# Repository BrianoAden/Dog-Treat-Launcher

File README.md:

<h1>Dog Treat Dispenser</h1>
<p> This project was for my EDES 301 class. Following is a link to the Hackster.io page I put up detailing the physical build of my project.</p>
<a href="https://www.hackster.io/aden-briano/edes301-dog-treat-launcher-bcfb15">Dog Treat Launcher</a>
<p> Now, I will walk you through the software build required to run this project!</p> 

<h2> Setup </h2>
<p> You are going to need to install the operating system on your PocketBeagle. You will need an SD card and SD card flashing software, like Etcher. 
Download bone-debian-10.11-iot-armhf-2022-02-03-4gb.img.xz from <a href="https://rcn-ee.com/rootfs/bb.org/testing/2022-02-03/buster-iot/">OS</a>. 
Use Etcher to flash your SD card. You can now insert your SD card into your PocketBeagle and plug your PocketBeagle into your laptop. 
Great! Now we can get started. You will need to use the Cloud9 IDE to code on the PocketBeagle using Python. Navigate to http://192.168.6.2:3000/ 
in your browser if you're on mac, or http://192.168.7.2:3000/ if you're on windows. You will also need your Beagle to be connected to the internet for this project. 
There are online resources on how to do this, so I won't walk through it. Once you're on Cloud9, run the following commands.</p>
<p>
                                            $ sudo apt-get update <br>
                                            $ sudo apt-get install build-essential python-dev python-setuptools python-smbus -y <br>
                                            $ sudo apt-get install python-pip python3-pip -y <br>
                                            $ sudo apt-get install zip -y <br>
                                            $ sudo pip3 install --upgrade setuptools <br>
                                            $ sudo pip3 install --upgrade Adafruit_BBIO <br>
                                            $ sudo pip3 install adafruit-blinka <br>
</p>
<p>
Now copy this github repo onto your PocketBeagle using the following command <br>
                                            $ git clone https://github.com/BrianoAden/EDES301 <br>
<h2> Package Installation </h2>
In order to run our project, we need to install the following packages: SpeechRecognition, PyAudio. <br> Let's begin the installation process. Run the following commands. <br>
<br>
$ sudo apt-get update <br>
$ sudo apt-get install -y swig libpulse-dev libasound2-dev <br>
$ sudo apt-get install libportaudio0 libportaudio2 libportaudiocpp0 portaudio19-dev <br>
$ sudo apt-get python-dev <br>
$ sudo python pyaudio/setup.py install <br>
$ sudo python3 -m pip install SpeechRecognition==3.9.0 <br>
<br>

Plug in your USB microphone. Let's check if it's recognized by the PocketBeagle. Run the following command. <br>
$ arecord -l <br>
You should see the following in your output. <br>
<br>
card 1: Device [USB PnP Sound Device], device 0: USB Audio [USB Audio] <br>
  Subdevices: 1/1 <br>
  Subdevice #0: subdevice #0 <br>
<br>
Good, our microphone is almost ready! We just need to set it as our default device. Run the following command. <br>
<br>
$ nano ~/.asoundrc <br>
<br>
Now write in the following. <br>

 <br>

Redundancy is resiliency, so run this just to be safe. <br>
$ sudo apt-get install -y python-pyaudio python3-pyaudio <br>

Now we should be good to go!
</p>
<h2> Software Operation </h2>
Note! You are required to be connected to the internet to run this project, as the recognize_google() method used by SpeechRecognition requires the internet.
If you manage to connect to the internet through your laptop, but when you reboot your PocketBeagle it disconnects, try running the following commands. <br>
<br>
$ sudo dhclient usb1 <br>
<br>
It's going to ask for a password. The password is temppwd. <br>
If you want to run the program, type sudo ./run into your terminal while in the treat_launcher directory. If this doesn't work, run chmod 755 ./run
to make it executable. To auto-run on boot, perform the following. <br>
<br>
$ sudo crontab -e <br>
<br>
Write the following at the bottom of the file <br>
<br>
@reboot sleep 30 && bash /var/lib/cloud9/EDES301/project_01/python/treat_launcher/run > /var/lib/cloud9/logs/cronlog 2>&1<br>
<br>
Now reboot and it should be good! Run the following to kill the processes. <br>
<br>
$ ps -ef <br>
$ sudo kill -9 (process id(s)) <br>
<br>
Now, you should be set to run the project. In each file under EDES301/project_01/python, there are tests you can use to debug a component.
I hope everything goes well, and I hope your dog loves it! Good luck building!

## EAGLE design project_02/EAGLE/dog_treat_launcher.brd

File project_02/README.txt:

Dog Treat Launcher PCB

You want to manufacture this PCB??? Wow you must really love your dog! Or you're just curious and wanted to read this file. Well, in the folder that you found this README inside, "project_02", there are three folders. Inside docs are just some screenshots of different parts of the board. Inside EAGLE, you will find the library I used to create the board, as well as the board's schematic and brd file. Inside MFG are the gerber files that you can use if you feel like spending a pretty penny on manufacturing this board. 
This board is designed after the Dog Treat Launcher I designed and developed in project_01. If you care to learn more about that project, please read the README file in project_01. Following is the link to the hackster page I put up for the project. https://www.hackster.io/aden-briano/edes301-dog-treat-launcher-bcfb15 Enjoy!

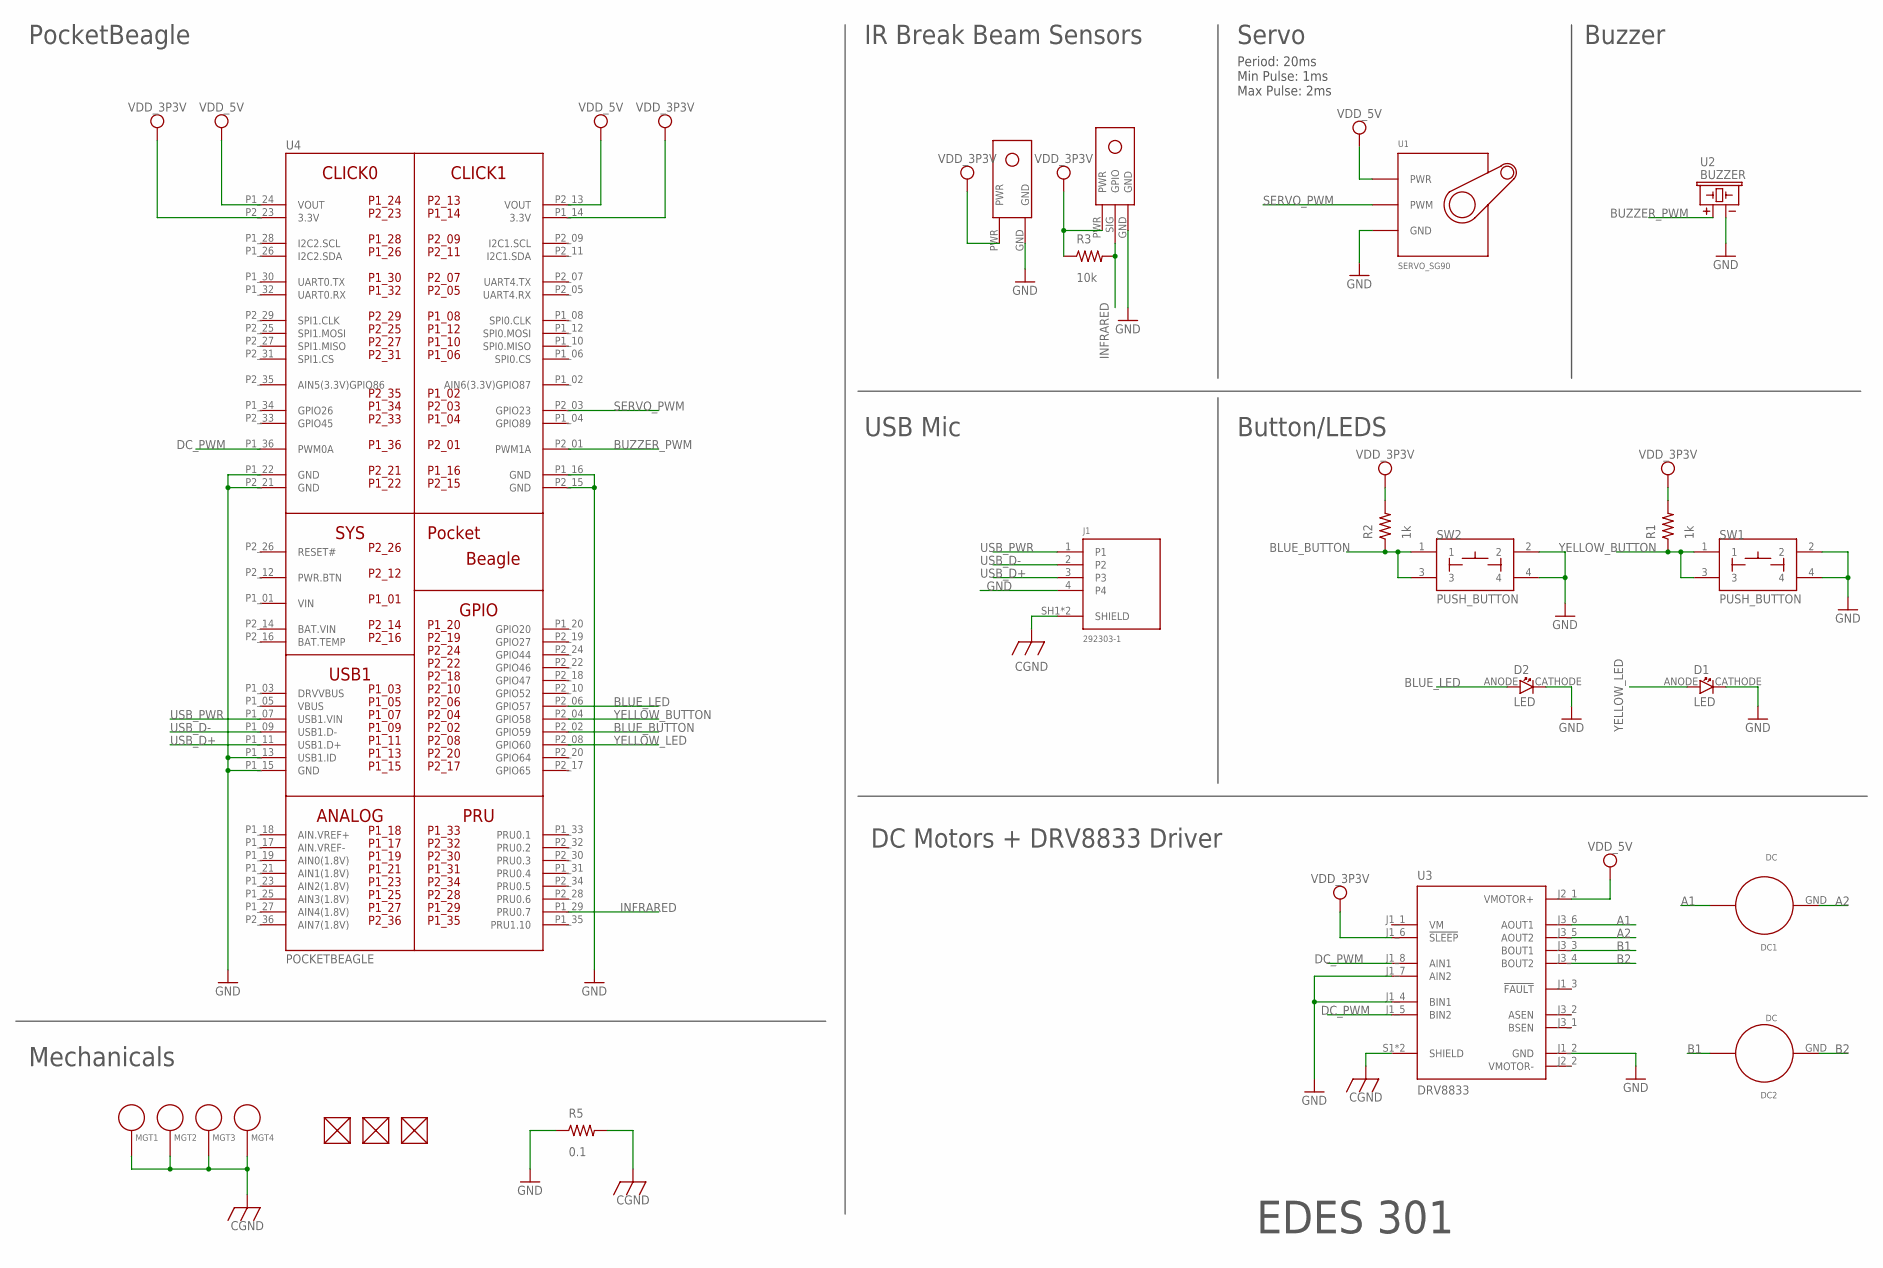
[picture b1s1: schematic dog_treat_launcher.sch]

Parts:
D1, D2: LED; EIA-STD
DC1, DC2: DC; DC_FOOTPRINT
FUD1, FUD2, FUD3: FIDUCIAL; FIDUCIAL_40MIL
IR_T1: IR_TRANSMITTER; IR_T
IT_R1: IR_RECIEVER; IR_R
J1: 292303-1; TE_292303-1
MGT1, MGT2, MGT3, MGT4: MOUNTING_HOLE
R1, R2: 1k; R0402
R3: 10k; R0402
R5: 0.1; R0402
SW1, SW2: PUSH_BUTTON; BUTTON_12.5MM
U1: SERVO_SG90; SERVO-X1
U2: BUZZER; BUZZER_6.5MM
U3: DRV8833; MODULE_3297
U4: POCKETBEAGLE

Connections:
A1: DC1.PWR, U3.J3_6 (AOUT1)
A2: DC1.GND, U3.J3_5 (AOUT2)
B1: DC2.PWR, U3.J3_3 (BOUT1)
B2: DC2.GND, U3.J3_4 (BOUT2)
BAT.VIN: U4.P2_14 (BAT.VIN)
BLUE_BUTTON: R2.1, SW2.1, SW2.3, U4.P2_02 (GPIO59)
BLUE_LED: D2.ANODE, U4.P2_06 (GPIO57)
BUZZER_PWM: U2.+, U4.P2_01 (PWM1A)
CGND: J1.SH1 (SHIELD), J1.SH2 (SHIELD), MGT1.P$1, MGT2.P$1, MGT3.P$1, MGT4.P$1, R5.2, U3.S1 (SHIELD), U3.S2 (SHIELD)
DC_PWM: U3.J1_5 (BIN2), U3.J1_8 (AIN1), U4.P1_36 (PWM0A)
GND: D1.CATHODE, D2.CATHODE, IR_T1.GND, IT_R1.GND, J1.4, R5.1, SW1.2, SW1.4, SW2.2, SW2.4, U1.GND, U2.-, U3.J1_2 (GND), U3.J1_4 (BIN1), U3.J1_7 (AIN2), U4.P1_13 (USB1.ID), U4.P1_15 (GND), U4.P1_16 (GND), U4.P1_22 (GND), U4.P2_15 (GND), U4.P2_21 (GND)
INFRARED: IT_R1.SIG (GPIO), R3.2, U4.P1_29 (PRU0.7)
SERVO_PWM: U1.SIG (PWM), U4.P2_03 (GPIO23)
USB_D+: J1.3, U4.P1_11 (USB1.D+)
USB_D-: J1.2, U4.P1_09 (USB1.D-)
USB_PWR: J1.1, U4.P1_07 (USB1.VIN)
VDD_3P3V: IR_T1.PWR, IT_R1.PWR, R1.2, R2.2, R3.1, U3.J1_6 (!SLEEP), U4.P1_14 (3.3V), U4.P2_23 (3.3V)
VDD_5V: U1.PWR, U3.J2_1 (VMOTOR+), U4.P1_24 (VOUT), U4.P2_13 (VOUT)
VIN: U4.P1_01 (VIN)
VMOTOR-: U3.J2_2 (VMOTOR-)
YELLOW_BUTTON: R1.1, SW1.1, SW1.3, U4.P2_04 (GPIO58)
YELLOW_LED: D1.ANODE, U4.P2_08 (GPIO60)

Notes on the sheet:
PocketBeagle
IR Break Beam Sensors
Servo
Button/LEDS
USB Mic
DC Motors + DRV8833 Driver
Buzzer
Period: 20ms Min Pulse: 1ms Max Pulse: 2ms
EDES 301
Mechanicals

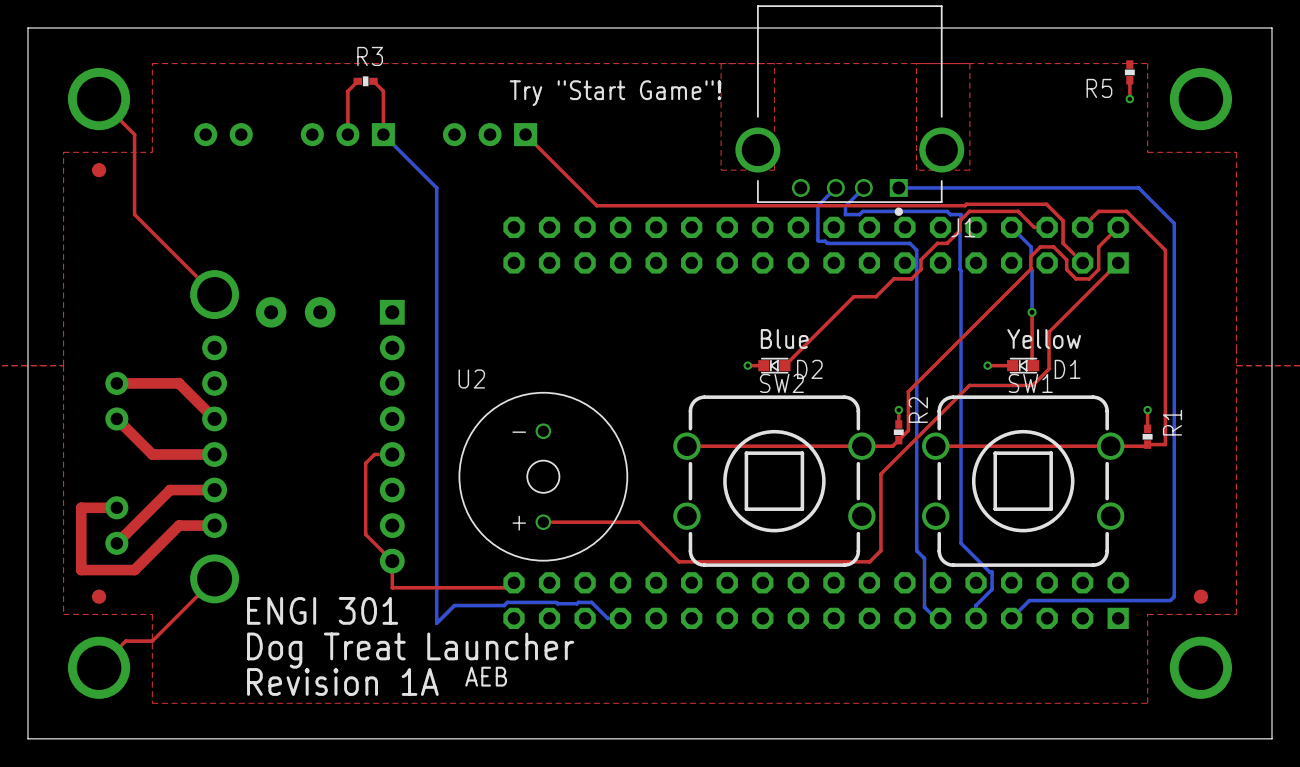
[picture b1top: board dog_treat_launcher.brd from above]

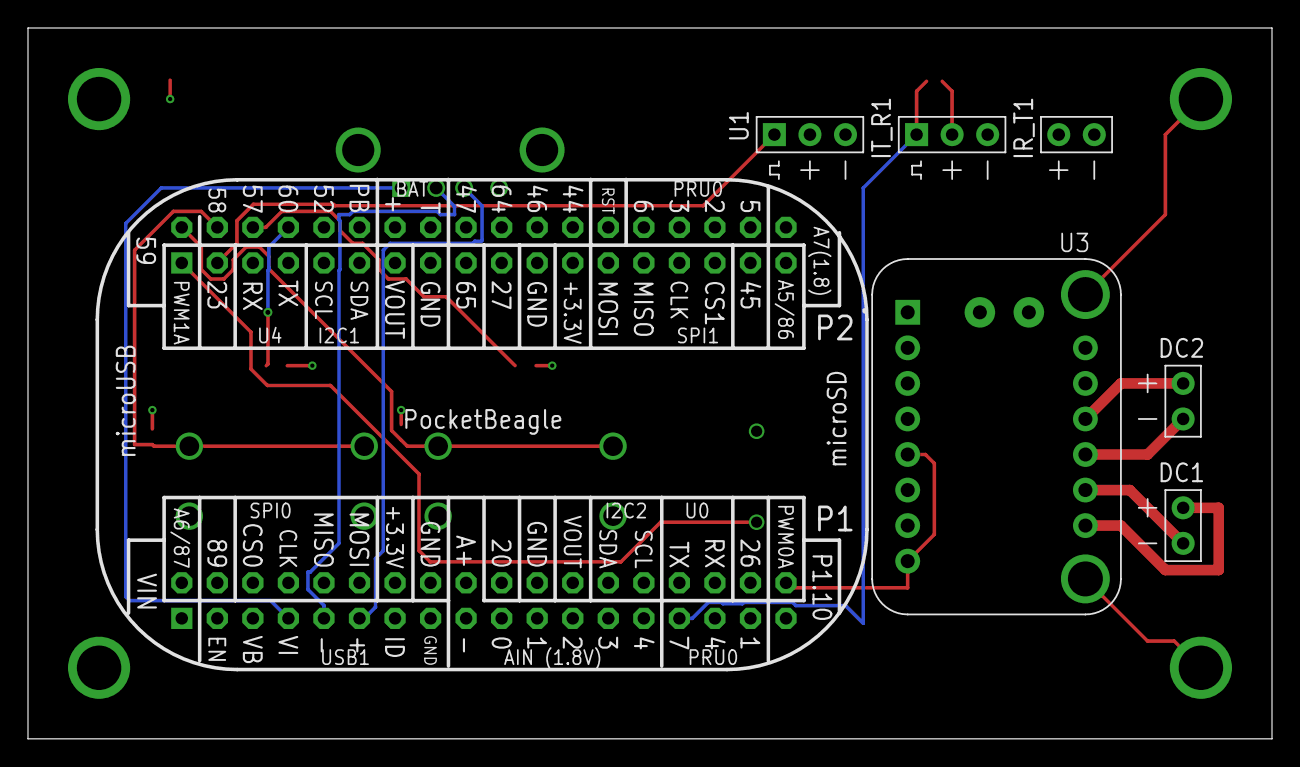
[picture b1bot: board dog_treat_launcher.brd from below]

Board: 4 copper layers, 88.9 x 50.8 mm, 24 parts (7 on the bottom side), 19 nets.

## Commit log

2024-09-20 Updating README.md
2024-10-01 created README.md file for project
2024-10-01 Added Project Proposal
2024-10-02 Added simple_calc.py
2024-10-07 worked on simple_calc.py and imported project proposal
2024-10-07 Added updated Project Proposal
2024-10-09 added homework 4 code
2024-10-23 Added software framework
2024-12-06 added code for treat_launcher, as well as in class code
2024-12-08 modifying README
2024-12-08 modified README
2024-12-08 continuing to update README
2024-12-08 README
2024-12-08 fixed file documentation and updated README
2024-12-08 final change to run script
2024-12-08 final change to README
2024-12-08 final changes
2024-12-08 done
2024-12-08 added internet connection steps in README
2024-12-19 Add project_02
